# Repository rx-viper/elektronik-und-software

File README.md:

# REXUS project VIPER: Elektronik and Software

### Structure of this repository

#### *boards*
* KiCAD and mechanical files for all PCBs used in the project.

#### *software/onboard*
* Code files of microcontroller software inside the rexus module.

#### *software/groundstation*
* Code files for the groundstation software (C++/Qt).

#### *docs*
* Documentation for all above.

### HowTo do changes to this repository

* Create a new branch: `git checkout -b feature/something-i-changed`
* Do your changes.
* Tell git what files your changed and want to commit: `git add my/file.changed my/other/file.changed`
* Commit your changes: `git commit -m "Description of my changes"`
* Push your changes to Github: `git push`
* Go to Github and create a new *Pull request* from your new branch to the *master* branch.
* Wait for someone to review and merge your Pull Request.
* Then checkout the *master* brach and pull the changes from Github: `git checkout master && git pull`

Use markdown syntax for text files and `*.md` file extension.

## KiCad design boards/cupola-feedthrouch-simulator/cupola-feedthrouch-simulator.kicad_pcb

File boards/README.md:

# rexus-viper-elektronik
Rexus Viper Elektronik Projekt

## Temperature Sensor Board
* LTC2984
* <-> 6x PT-100 4-wire
* -> 5V power supply
* <- SPI data out

## Mainboard
* -> Pressure sensor (SPI/I2C)
* -> Force sensor (analog/SPI/I2C)
* -> 5x Temperature sensor SPI (Temperature Sensor Board)
* -> Heat probe voltage and current sensing
* -> DS18B20 Temperature sensors (1-wire bus)
* 3.3V regulator
* STM32F429VI microcontroller
* Data storage (flash memory chip)
* <-> RXSM communication
* <- Raspberry Pi (UART)
* -> 5V power supply
* -> Status LEDs
* <- Control panel

## Powerboard
* -> Battery
* -> RXSM power
* 3x 60W 24V step-up converter
* <- Heat probe
* <- Motor power
* -> Motor control
* <- Battery heater
* <- Mainboard power
* <- Raspbery Pi power
* <- Camera power
* <- Camera light
* -> Camera control
* -> Heat probe control
* <- Heat probe voltage and current sensing

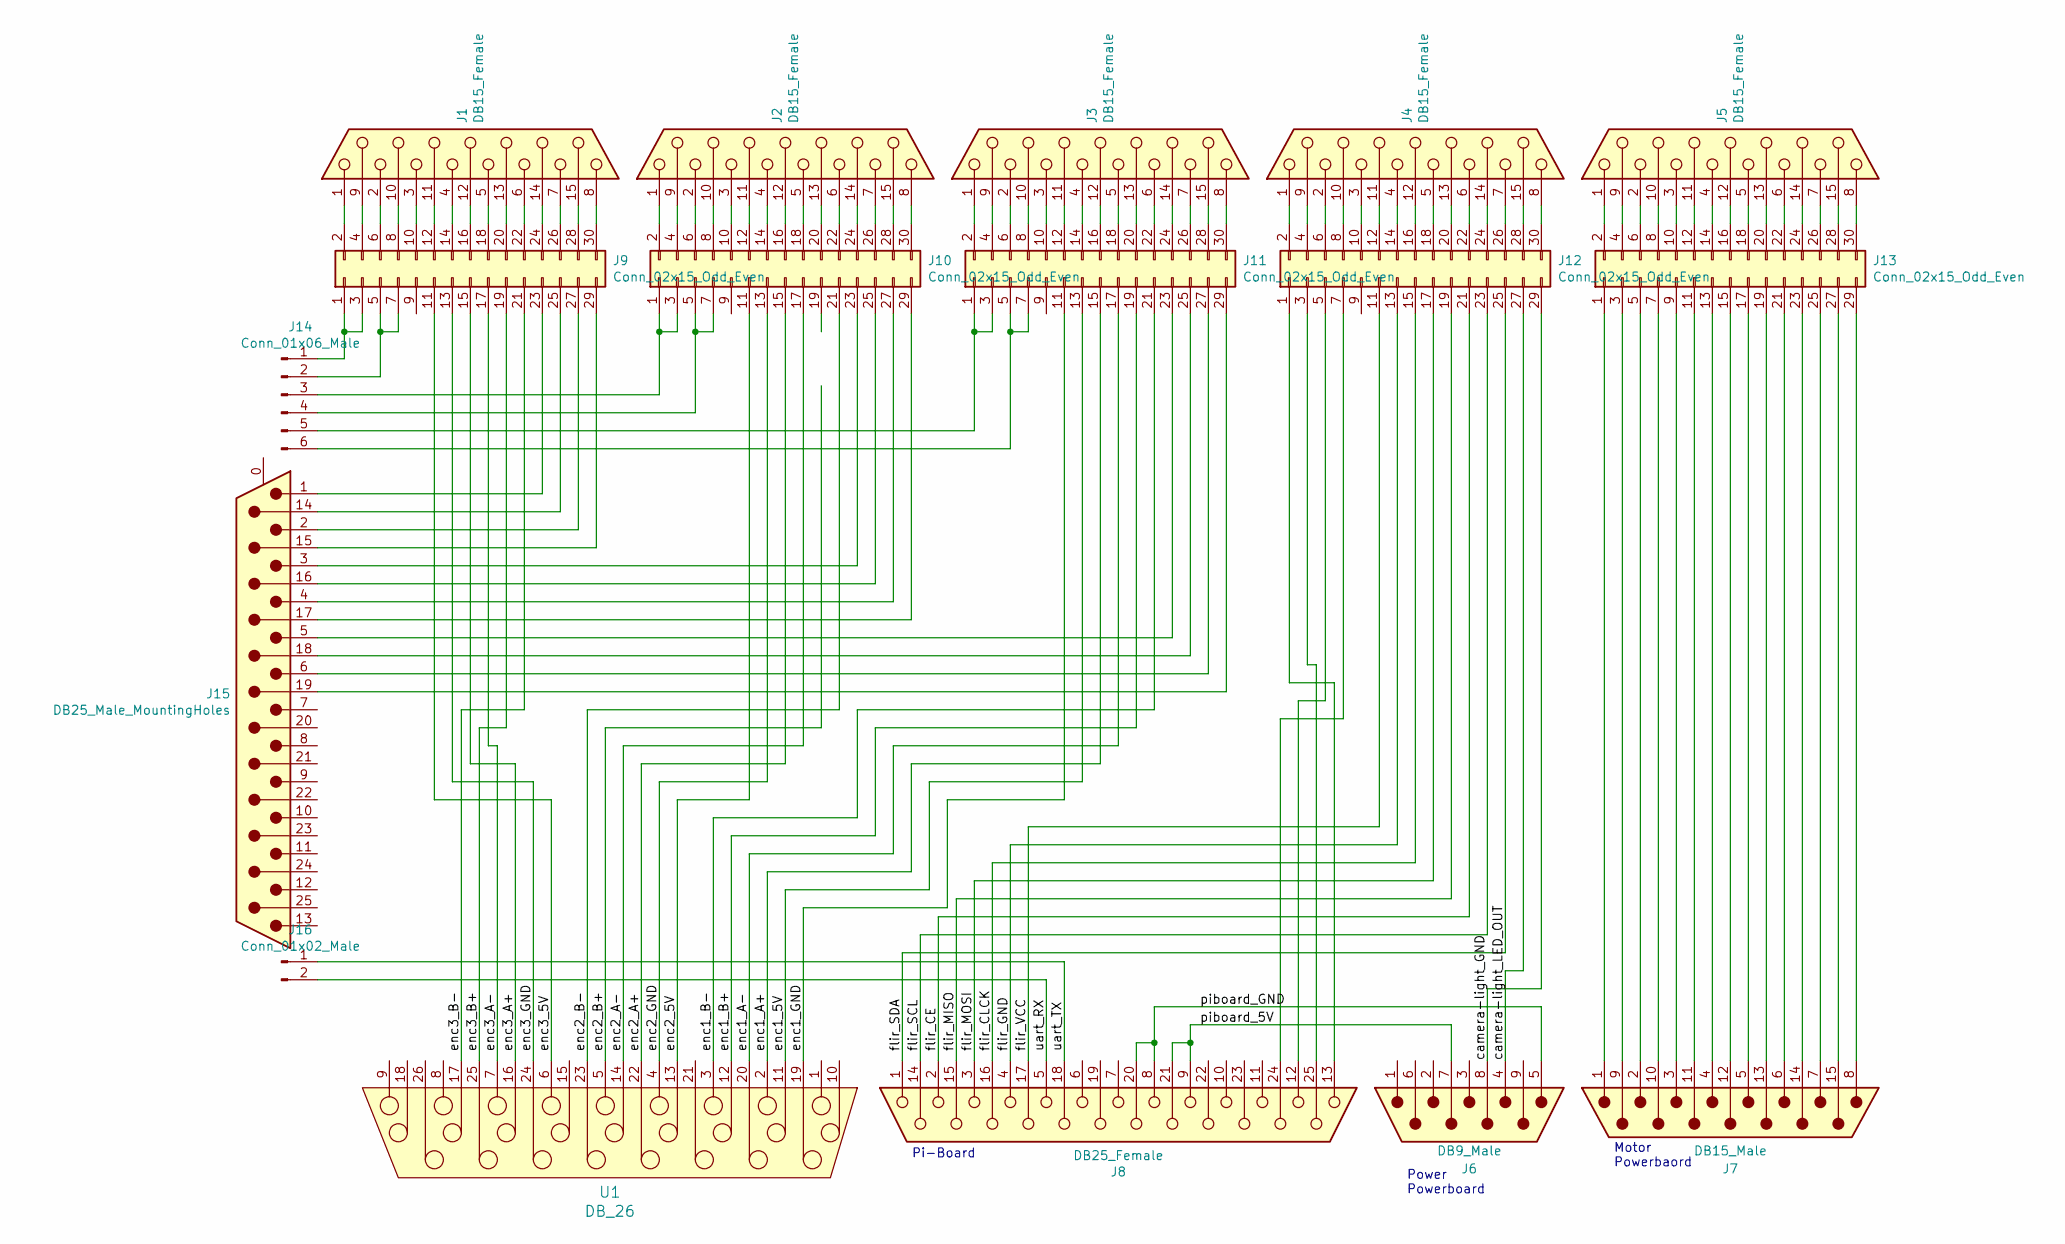
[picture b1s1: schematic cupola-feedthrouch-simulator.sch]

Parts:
J1, J2, J3, J4, J5: DB15_Female; DSUB-15_Female_Vertical_P2.77x2.84mm_MountingHoles
J6: DB9_Male; DSUB-9_Male_Vertical_P2.77x2.84mm_MountingHoles
J7: DB15_Male; DSUB-15_Male_Vertical_P2.77x2.84mm_MountingHoles
J8: DB25_Female; DSUB-25_Female_Vertical_P2.77x2.84mm_MountingHoles
J9, J10, J11, J12, J13: Conn_02x15_Odd_Even; PinHeader_2x15_P2.54mm_Vertical
J14: Conn_01x06_Male; PinHeader_1x06_P2.54mm_Vertical
J15: DB25_Male_MountingHoles; DSUB-25_Male_Vertical_P2.77x2.84mm_MountingHoles
J16: Conn_01x02_Male; PinHeader_1x02_P2.54mm_Vertical
U1: DB_26; DSUB-26-HD_Male_Vertical_P2.29x1.98mm_MountingHoles

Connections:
/camera-light_GND: J6.8, J12.29
/camera-light_LED_OUT: J6.4, J12.27
/enc1_5V: J11.13, U1.11
/enc1_A+: J11.15, U1.2
/enc1_A-: J11.17, U1.20
/enc1_B+: J11.19, U1.12
/enc1_B-: J11.21, U1.3
/enc1_GND: J11.11, U1.19
/enc2_5V: J10.11, U1.13
/enc2_A+: J10.15, U1.22
/enc2_A-: J10.17, U1.14
/enc2_B+: U1.5
/enc2_B-: J10.21, U1.23
/enc2_GND: J10.13, U1.4
/enc3_5V: J9.11, U1.6
/enc3_A+: J9.15, U1.16
/enc3_A-: J9.17, U1.7
/enc3_B+: J9.19, U1.25
/enc3_B-: J9.21, U1.17
/enc3_GND: J9.13, U1.24
/flir_CE: J8.2, J12.21
/flir_CLCK: J8.16, J12.15
/flir_GND: J8.4, J12.13
/flir_MISO: J8.15, J12.19
/flir_MOSI: J8.3, J12.17
/flir_SCL: J8.14, J12.23
/flir_SDA: J8.1, J12.25
/flir_VCC: J8.17, J12.11
/piboard_5V: J6.7, J8.9, J8.21
/piboard_GND: J6.5, J8.8, J8.20
/uart_RX: J8.5, J16.2
/uart_TX: J8.18, J16.1
unnamed: J1.1, J9.2
unnamed: J1.2, J9.6
unnamed: J1.3, J9.10
unnamed: J1.4, J9.14
unnamed: J1.5, J9.18
unnamed: J1.6, J9.22
unnamed: J1.7, J9.26
unnamed: J1.8, J9.30
unnamed: J1.9, J9.4
unnamed: J1.10, J9.8
unnamed: J1.11 (P111), J9.12
unnamed: J1.12, J9.16
unnamed: J1.13, J9.20
unnamed: J1.14, J9.24
unnamed: J1.15, J9.28
unnamed: J10.1, J10.3, J14.3
unnamed: J2.1, J10.2
unnamed: J2.9, J10.4
unnamed: J10.5, J10.7, J14.4
unnamed: J2.2, J10.6
unnamed: J2.10, J10.8
unnamed: J2.3, J10.10
unnamed: J2.11 (P111), J10.12
unnamed: J2.4, J10.14
unnamed: J2.12, J10.16
unnamed: J2.5, J10.18
unnamed: J2.13, J10.20
unnamed: J2.6, J10.22
unnamed: J10.23, J15.3
unnamed: J2.14, J10.24
unnamed: J10.25, J15.16
unnamed: J2.7, J10.26
unnamed: J10.27, J15.4
unnamed: J2.15, J10.28
unnamed: J10.29, J15.17
unnamed: J2.8, J10.30
unnamed: J11.1, J11.3, J14.5
unnamed: J3.1, J11.2
unnamed: J3.9, J11.4
unnamed: J11.5, J11.7, J14.6
unnamed: J3.2, J11.6
unnamed: J3.10, J11.8
unnamed: J3.3, J11.10
unnamed: J3.11 (P111), J11.12
unnamed: J3.4, J11.14
unnamed: J3.12, J11.16
unnamed: J3.5, J11.18
unnamed: J3.13, J11.20
unnamed: J3.6, J11.22
unnamed: J11.23, J15.5
unnamed: J3.14, J11.24
unnamed: J11.25, J15.18
unnamed: J3.7, J11.26
unnamed: J11.27, J15.6
unnamed: J3.15, J11.28
unnamed: J11.29, J15.19
unnamed: J3.8, J11.30
unnamed: J8.13, J12.1
unnamed: J4.1, J12.2
unnamed: J8.25, J12.3
unnamed: J4.9, J12.4
unnamed: J8.12, J12.5
unnamed: J4.2, J12.6
unnamed: J8.24, J12.7
unnamed: J4.10, J12.8
unnamed: J4.3, J12.10
unnamed: J4.11 (P111), J12.12
unnamed: J4.4, J12.14
unnamed: J4.12, J12.16
unnamed: J4.5, J12.18
unnamed: J4.13, J12.20
unnamed: J4.6, J12.22
unnamed: J4.14, J12.24
unnamed: J4.7, J12.26
unnamed: J4.15, J12.28
unnamed: J4.8, J12.30
unnamed: J7.1, J13.1
unnamed: J5.1, J13.2
unnamed: J7.9, J13.3
unnamed: J5.9, J13.4
unnamed: J7.2, J13.5
unnamed: J5.2, J13.6
unnamed: J7.10, J13.7
unnamed: J5.10, J13.8
unnamed: J7.3, J13.9
unnamed: J5.3, J13.10
unnamed: J7.11 (P111), J13.11
unnamed: J5.11 (P111), J13.12
unnamed: J7.4, J13.13
unnamed: J5.4, J13.14
unnamed: J7.12, J13.15
unnamed: J5.12, J13.16
unnamed: J7.5, J13.17
unnamed: J5.5, J13.18
unnamed: J7.13, J13.19
unnamed: J5.13, J13.20
unnamed: J7.6, J13.21
unnamed: J5.6, J13.22
unnamed: J7.14, J13.23
unnamed: J5.14, J13.24
unnamed: J7.7, J13.25
unnamed: J5.7, J13.26
unnamed: J7.15, J13.27
unnamed: J5.15, J13.28
unnamed: J7.8, J13.29
unnamed: J5.8, J13.30
unnamed: J9.1, J9.3, J14.1
unnamed: J9.5, J9.7, J14.2
unnamed: J9.23, J15.1
unnamed: J9.27, J15.2
unnamed: J9.25, J15.14
unnamed: J9.29, J15.15

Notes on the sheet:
Motor Powerbaord
Power Powerboard
Pi-Board

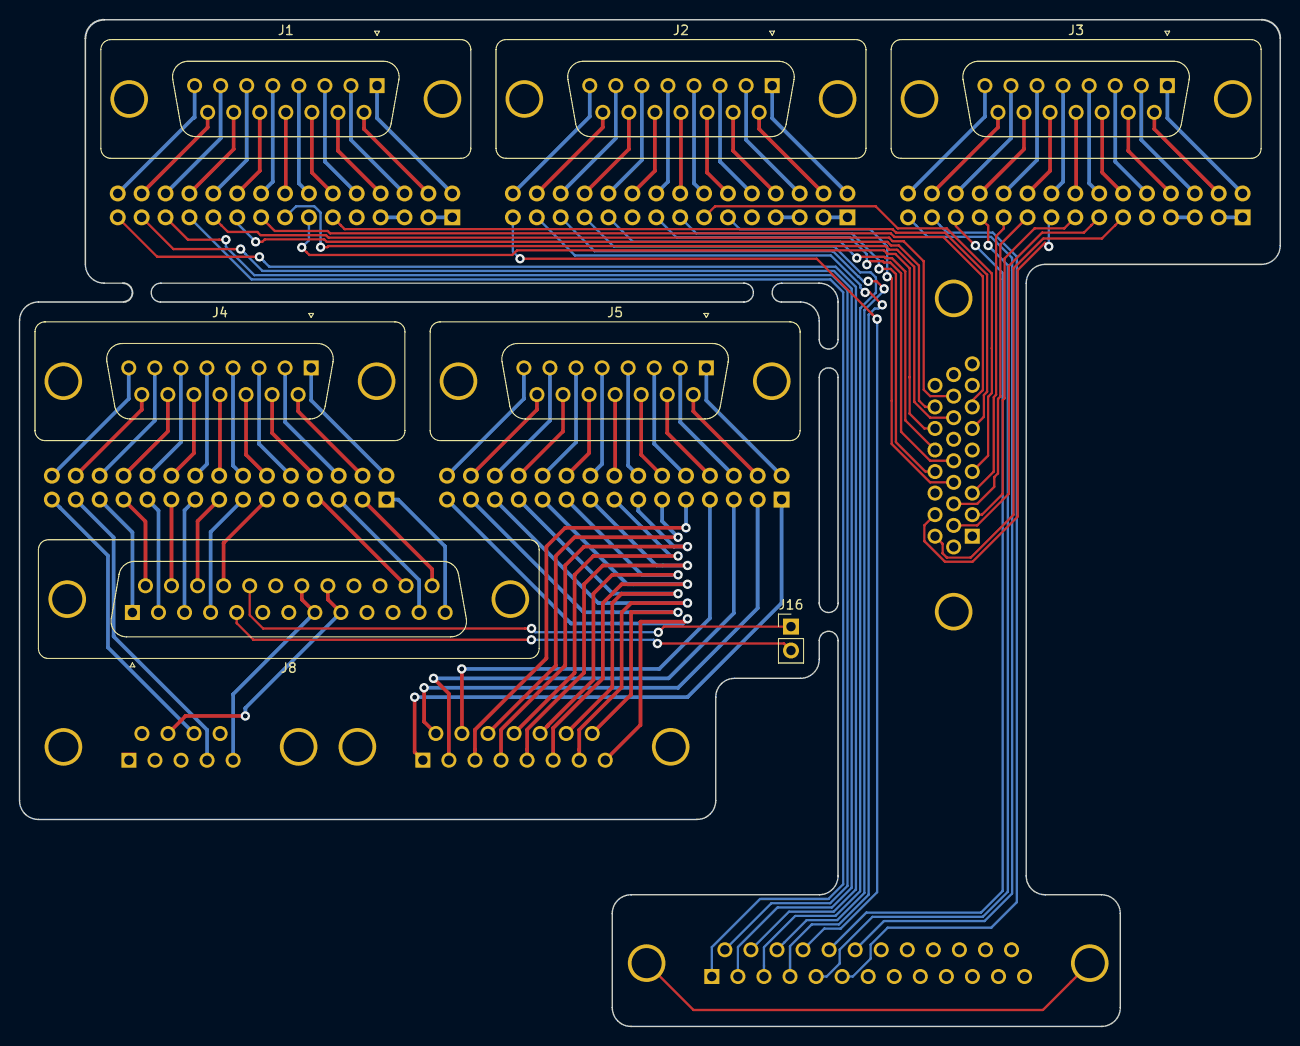
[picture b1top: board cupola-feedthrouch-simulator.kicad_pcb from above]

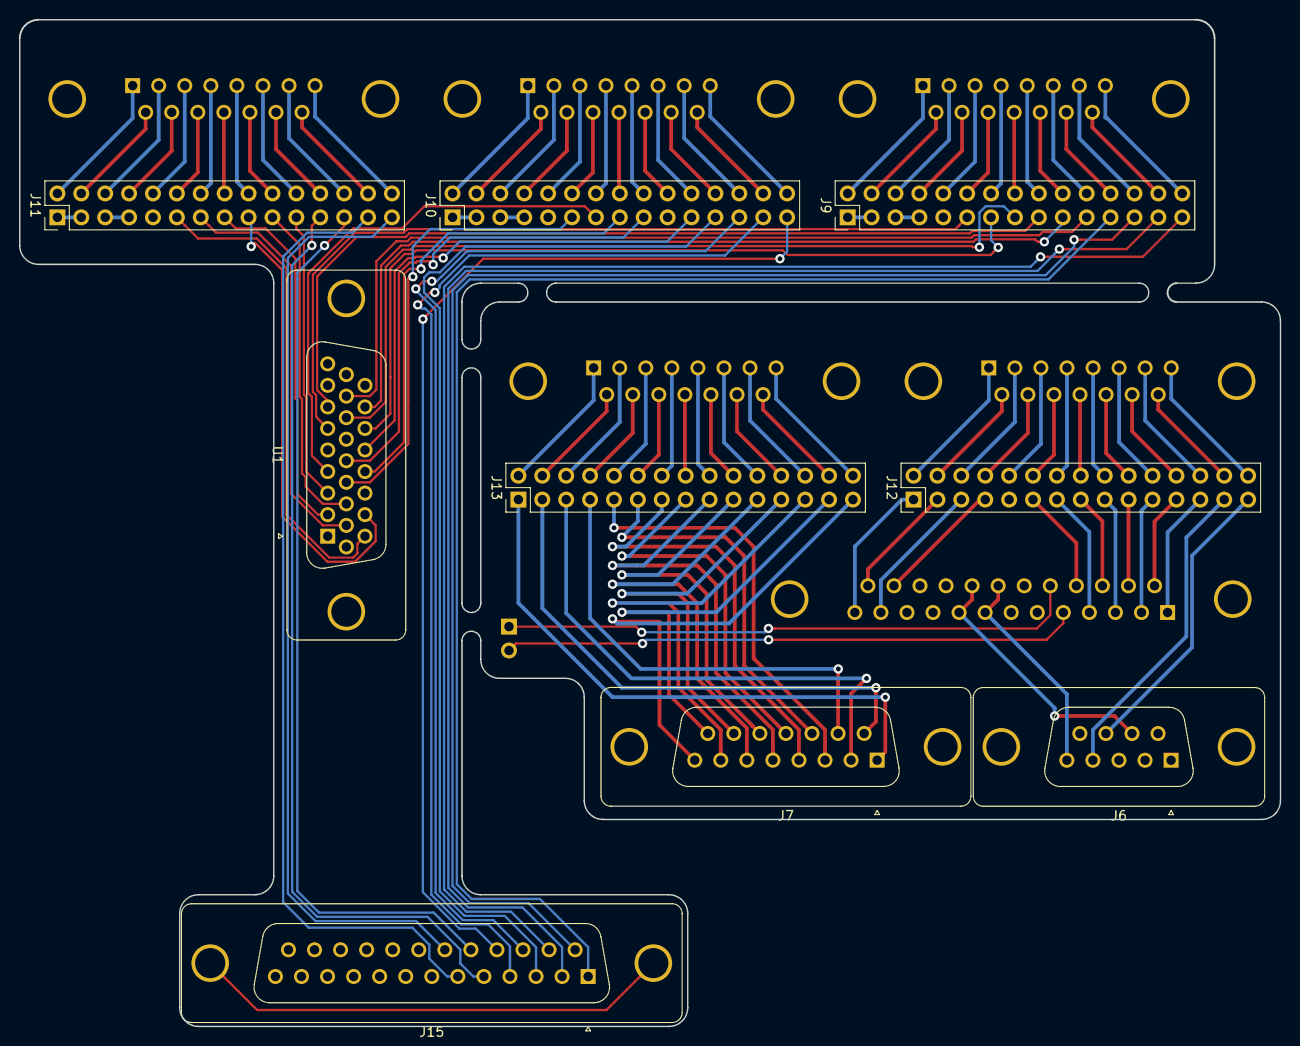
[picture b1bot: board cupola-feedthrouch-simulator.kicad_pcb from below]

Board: 2 copper layers, 134.0 x 107.0 mm, 16 parts (9 on the bottom side), 143 nets.

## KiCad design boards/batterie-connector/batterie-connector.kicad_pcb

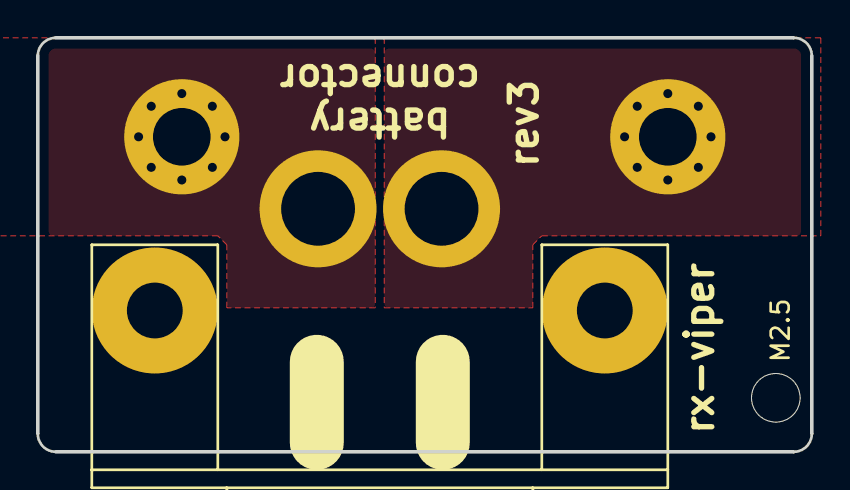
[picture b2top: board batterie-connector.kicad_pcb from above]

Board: 2 copper layers, 43.0 x 23.0 mm, 4 parts (0 on the bottom side), 2 nets, no tracks yet.

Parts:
H101: M2.5; MountingHole_2.7mm_M2.5_DIN965
J101: 2W2C; D-Sub-Combo_2W2C
J102: +; MountingHole_3.2mm_M3_Pad_Via
J103: -; MountingHole_3.2mm_M3_Pad_Via

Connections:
/MINUS: J101.2, J103.1
/PLUS: J101.1, J102.1

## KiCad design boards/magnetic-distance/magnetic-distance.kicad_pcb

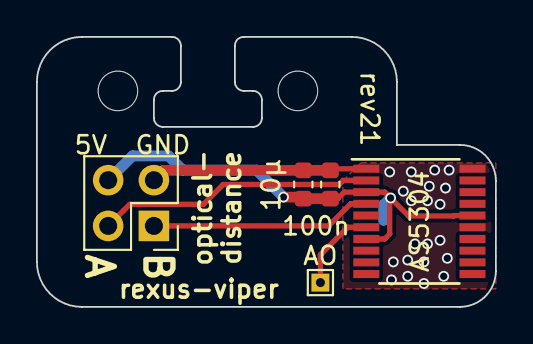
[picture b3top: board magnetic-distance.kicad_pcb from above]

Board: 2 copper layers, 25.5 x 15.0 mm, 8 parts (1 on the bottom side), 5 nets.

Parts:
C101: 100n; C_0603_1608Metric
C102: 10µ; C_0603_1608Metric
H101, H102: M2; MountingHole_2.2mm_M2
J101: Cable; PinHeader_2x02_P2.54mm_Vertical
R_HEAT101: 100; R_0805_2012Metric
TP101: AO; TestPoint_THTPad_1.0x1.0mm_Drill0.5mm
U101: AS5304; TSSOP-20_4.4x6.5mm_P0.65mm

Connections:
+5V: C101.1, C102.1, J101.4, R_HEAT101.1, U101.3, U101.7, U101.16
/A: J101.2, U101.2
/AO: TP101.1, U101.6
/B: J101.1, U101.4
GND: C101.2, C102.2, J101.3, R_HEAT101.2, U101.1, U101.15, U101.20

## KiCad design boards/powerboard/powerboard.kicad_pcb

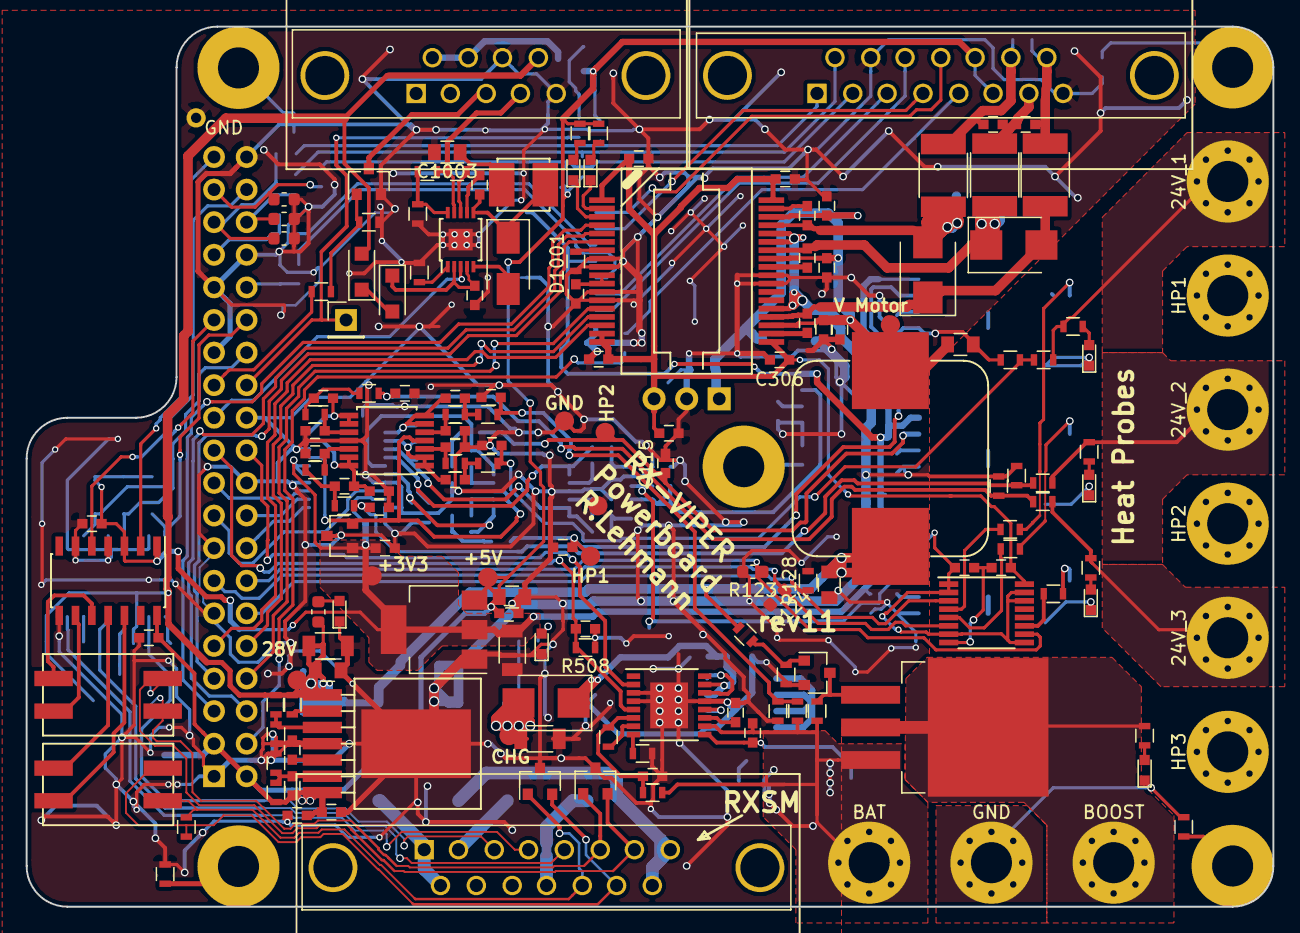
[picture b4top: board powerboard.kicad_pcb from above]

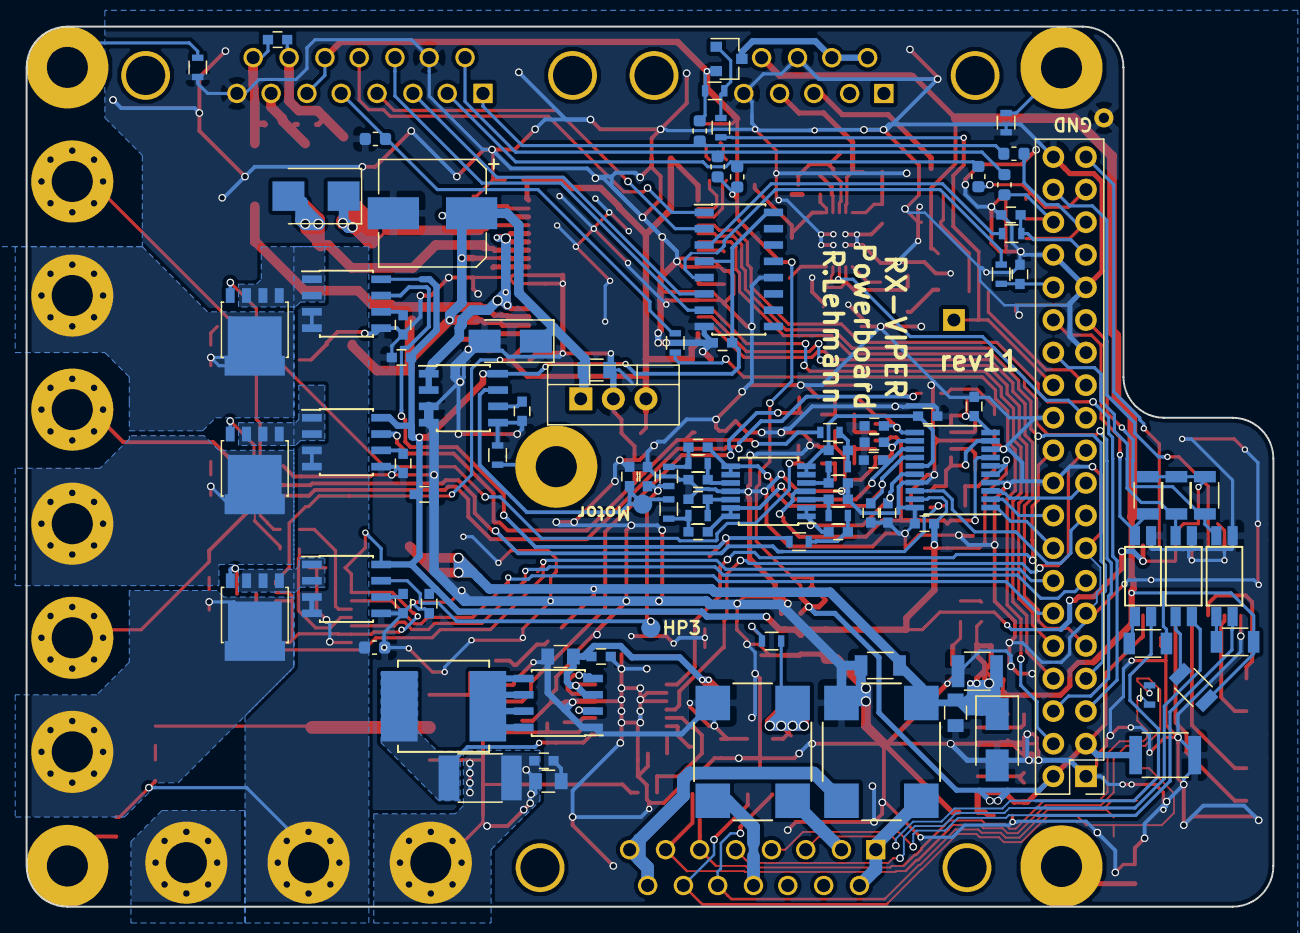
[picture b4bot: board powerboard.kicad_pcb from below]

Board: 2 copper layers, 97.2 x 68.6 mm, 268 parts (97 on the bottom side), 174 nets.

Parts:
C101: 10µ; C_1206
C102: 4µ7 1206 50V; C_1206
C103: 1µ; C_0805
C104: 10µ oder 4µ7 Tantal; C_0805
C105, C109, C302, C304, C305, C306, C308, C309, C310, C312, C315, C504, C506, C701, C801, C802, C803, C901, C902, C1002, C1201, C1202: 100n; C_0603
C106: 470n; C_0805
C107, C121: 2n7; C_0603
C108: 22µ Tantal; C_1206
C110, C111, C112, C113, C114, C115, C116, C117, C205, C910, C911, C912, C913, C914, C915, C916, C917: 10n; C_0603
C118: 10µ 1210; C_1210
C119: 1µ 0805 50V; C_0805
C120: 50SVPK68M; CP_Elec_8x10.5
C122, C123, C124: 22n; C_0603_1608Metric
C201: 10µ/40V; C_1206
C202: 1µ/40V; C_0805
C203, C204: 22n; C_0603
C206: 100µ/10V; C_1812
C207, C307, C314, C702, C1001: 1µ; C_0603
C301: 4µ7 0805; C_0805
C303: 10µ; C_0603
C313: 4µ7 0805; C_0603
C316, C317, C318: 100p; C_0603
C319, C804, C805, C806: 1n; C_0603
C501: 68n; C_0603
C502: 47n; C_0603
C503: 10µ 0805 35V; C_0805
C505: 10µ; C_0805
C507: 470n; C_0603
C508, C1101, C1102, C1103, C1104, C1105, C1106, C1107, C1108, C1109, C1110, C1111, C1112, C1113, C1114, C1115, C1116: 220n; C_0603
C1003: 4µ7 0805 50V; C_0805
D101: RX-PW; LED_0603
D102: RX-CHG; LED_0603
D103: BAT; LED_0603
D104, D105: SMAJ36A; D_SMA
D301, D302: LED; LED_0603
D304, D305, D306: SMBJ40CA; D_SMB_Standard
D501: MBRS360BT3G; D_SMB_Standard
D701, D702: ESD; SOT-23
D801: HP1; LED_0603
D802: HP2; LED_0603
D803: HP3; LED_0603
D1001: MBRA140T3; D_SMA_Standard
D1002, D1003: US1NWF; D_SOD-123F
FL101, FL102: 744272471; WE-SL5
FL701, FL702: 744228; WE-SL2
J101: RXSM experiment connector; DB15MD
J102: Powerboard <-> Mainboard; Pin_Header_Straight_2x20_Pitch2.54mm
J103: Cameraboard; DB9FD
J104: BLDC Motor; DB15FD
J105: BOOST; MountingHole_3.2mm_M3_Pad_Via
J106: Boost24V_EN; Pin_Header_Straight_1x01_Pitch2.54mm
J107: 24V_1; MountingHole_3.2mm_M3_Pad_Via
J108: 24V_2; MountingHole_3.2mm_M3_Pad_Via
J109: 24V_3; MountingHole_3.2mm_M3_Pad_Via
J110: BAT; MountingHole_3.2mm_M3_Pad_Via
J111: GND; MountingHole_3.2mm_M3_Pad_Via
J112, J113, J114, J115, J117: M3; MountingHole_3.2mm_M3_Pad
J810: HP1; MountingHole_3.2mm_M3_Pad_Via
J811: HP2; MountingHole_3.2mm_M3_Pad_Via
J812: HP3; MountingHole_3.2mm_M3_Pad_Via
L101: Coilcraft MSS1583-474; L_Coilcraft_1583_Handsoldering
L301, L302, L303: 742792515; L_1812
L501: Coilcraft XAL6060-223; L_Coilcraft_XAL60xx_Handsoldering
L1001: Coilcraft XAL4040-103; L_Coilcraft_XAL40xx_Handsoldering
Q101: SQM40031EL; TO-263-3Lead
Q102: DMN6140L; SOT-23
Q103: PMV27UPE; SOT-23
Q104: PMV55ENEA; SOT-23
Q503: IRF7343PBF; SOIC-8_3.9x4.9mm_Pitch1.27mm
Q801, Q802, Q803: BUK7Y4R8-60E; SOT-669_LFPAK
R101, R103, R126, R128, R508, R801, R802, R803, R807, R808, R809: 10k; R_0603
R102: 20k; R_0603
R104: 91k; R_0603
R105: 13k; R_0603
R106, R108, R113: 15k; R_0603
R107, R109, R110, R114, R130, R607, R608: 1k; R_0603
R111: 0; R_0603
R112, R129, R1002: 100k; R_0603
R115, R116, R117, R118, R120: NC; R_0603
R119, R121: 100; R_0603
R122: 0; R_0603_1608Metric
R123, R124, R125: 10k; R_0603_1608Metric
R127: 4k; R_0603
R131, R132, R133, R137: 4k7; R_0603_1608Metric
R134, R135, R136: 470; R_0603_1608Metric
R201: 68k1; R_0603
R202: 11k8; R_0603
R203: 43k2; R_0603
R204: 5k62; R_0603
R205: 1k07; R_0603
R301, R302: 470; R_0603
R303: 200k; R_0603
R504: 65k7; R_0603
R505: 8k2; R_0603
R506: 50k; R_0603
R507: 100m; R_1812
R601, R602, R603, R604, R605, R606: 10k 1206; R_1206
R1001: 140k; R_0603
R1003: 4k7; R_0603
R1004: 2R; R_0603
R1101, R1102, R1103, R1104, R1105, R1106, R1107, R1108, R1109, R1110, R1111, R1112, R1113, R1114, R1115, R1116: 47k; R_0603
TP101: 28V; Measurement_Point_Round-SMD-Pad_Small
TP102: CHG; Measurement_Point_Round-SMD-Pad_Small
TP103: +5V; Measurement_Point_Round-SMD-Pad_Small
TP104: +3V3; Measurement_Point_Round-SMD-Pad_Small
TP105, TP106: GND; Measurement_Point_Round-SMD-Pad_Small
TP107: HP3C; Measurement_Point_Round-SMD-Pad_Small
TP108: GND; Measurement_Point_Round-TH_Small
TP109: HP2C; Measurement_Point_Round-SMD-Pad_Small
TP110: HP1C; Measurement_Point_Round-SMD-Pad_Small
TP111: V_MOTOR; Measurement_Point_Round-SMD-Pad_Small
TP112: MOTORC; Measurement_Point_Round-SMD-Pad_Small
U101: LM1117-3.3; SOT-223
U102: DS26LV32AT; SOIC-16_3.9x9.9mm_Pitch1.27mm
U201: LMZ14203; 7TO-PMOD
U301: 7812SR-C; TO-220_Vertical
U302: DRV8332; HSSOP-36
U303, U801, U802, U803: ACS711; SOIC-8_3.9x4.9mm_Pitch1.27mm
U501: LTC4010; TSSOP-16-1EP_4.4x5mm_Pitch0.65mm
U601, U602, U603: PC3H7; SOP-4
U701: MAX13432EESD; SOIC-14_3.9x8.7mm_Pitch1.27mm
U901: AD7928; TSSOP-20_4.4x6.5mm_Pitch0.65mm
U902: REF3025; SOT-23
U1001: LT3592; MSOP-10-1EP_3x3mm_Pitch0.5mm
U1101, U1102: LMV324; TSSOP-14_4.4x5mm_Pitch0.65mm
U1201: CD40109B; TSSOP-16_4.4x5mm_Pitch0.65mm

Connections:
+2V5: U901.7, U902.2, U1101.4, U1102.4
+3V3: C108.1, C109.1, C701.1, C801.1, C802.1, C803.1, C901.1, C902.1, C1201.1, R601.2, R602.2, R603.2, TP104.1, U101.2, U101.4, U102.4, U102.16, U303.8, U701.1, U701.3, U801.8, U802.8, U803.8, U901.5, U901.6, U901.19, U902.1, U1201.1, U1201.2, U1201.7, U1201.9, U1201.14, U1201.15
+5V: C104.1, C105.1, C204.1, C205.1, C206.1, C207.1, C702.1, J102.2, J102.3, J104.6, J104.13, Q103.2, R129.2, R131.1, R132.1, R133.1, R204.1, R301.2, R302.2, TP103.1, U101.3, U201.7, U701.14
+12V: C302.1, C303.1, C304.1, C306.1, C312.1, C1202.1, U301.3, U302.1, U302.17, U302.18, U302.19, U302.36, U1201.16
/24V_BAT_1: J107.1, R113.1, R807.2
/24V_BAT_2: J108.1, R108.1, R808.2
/24V_BAT_3: J109.1, R106.1, R809.2
/BAT_10V: J105.1, Q101.2, R127.2
/BAT_raw: C505.1, C506.1, C507.1, J110.1, Q101.3, R101.1, R104.1, R504.1, R507.2, U501.10
/Boost24V_EN: J102.26, J106.1, R130.2
/Cam_Light_EN: J102.23, U1001.3
/Charge_EN: C501.1, J102.21, R508.2, U501.5
/Charge_status: J102.22, U501.2
/Encoder_A: C107.1, J102.32, R119.1
/Encoder_A+: J104.3, U102.6
/Encoder_A-: J104.11, U102.7
/Encoder_A_filter: R119.2, U102.5
/Encoder_B: C121.1, J102.33, R121.1
/Encoder_B+: J104.4, U102.2
/Encoder_B-: J104.12, U102.1
/Encoder_B_filter: R121.2, U102.3
/EndSwitch: J102.4, R111.1
/Hall_U: J104.1, R133.2, R134.1
/Hall_U_filter: C122.1, J102.35, R134.2
/Hall_V: J104.9, R132.2, R135.1
/Hall_V_filter: C123.1, J102.36, R135.2
/Hall_W: J104.2, R131.2, R136.1
/Hall_W_filter: C124.1, J102.37, R136.2
/LO: J102.28, R601.1, U601.4
/Lens_Heat_EN: J102.25, R110.2
/Motor1_Current: C117.1, R1104.2, TP112.1, U303.7
/Motor_U_N: J102.6, U302.5
/Motor_U_P: J102.5, U302.4
/Motor_V_N: J102.8, U302.14
/Motor_V_P: J102.7, U302.6
/Motor_W_N: J102.10, U302.15
/Motor_W_P: J102.9, U302.16
/Phase_U: C317.1, C318.2, J104.14, L301.2
/Phase_V: C316.1, C317.2, J104.7, L302.2
/Phase_W: C316.2, C318.1, J104.15, L303.2
/Powerboard Battery Charging/bat_bgate: Q503.2, U501.12
/Powerboard Battery Charging/bat_inductor: L501.1, Q503.5, Q503.6, Q503.7, Q503.8
/Powerboard Battery Charging/bat_sense: C507.2, L501.2, R507.1, U501.9
/Powerboard Battery Charging/bat_tgate: Q503.4, U501.14
/Powerboard Battery Charging/charge_power: C101.1, D501.2, FL102.2, R126.2, TP102.1
/Powerboard Motor Controller/VREG: C305.1, U302.10, U302.11
/Powerboard Motor Controller/V_IN: C106.1, C120.1, C301.1, C307.1, C313.1, C314.1, C315.1, D105.1, L101.2, TP111.1, U301.1, U302.21, U302.29, U302.34
/Powerboard_ADC/IN0: C910.1, C1105.1, U901.16, U1101.1, U1101.2
/Powerboard_ADC/IN1: C911.1, C1106.1, U901.15, U1101.6, U1101.7
/Powerboard_ADC/IN2: C912.1, C1107.1, U901.14, U1101.8, U1101.9
/Powerboard_ADC/IN3: C913.1, C1108.1, U901.13, U1101.13, U1101.14
/Powerboard_ADC/IN4: C914.1, C1113.1, U901.12, U1102.1, U1102.2
/Powerboard_ADC/IN5: C915.1, C1114.1, U901.11, U1102.6, U1102.7
/Powerboard_ADC/IN6: C916.1, C1115.1, U901.10, U1102.8, U1102.9
/Powerboard_ADC/IN7: C917.1, C1116.1, U901.9, U1102.13, U1102.14
/Powerboard_ADC_Filter/IN4: C113.1, R113.2, R114.1, R1109.2
/Powerboard_ADC_Filter/IN5: C110.1, R104.2, R105.1, R1110.2
/Powerboard_ADC_Filter/IN6: C111.1, R106.2, R107.1, R1111.2
/Powerboard_ADC_Filter/IN7: C112.1, R108.2, R109.1, R1112.2
/Powerboard_Heat_Probes/Probe1: D801.1, J810.1, Q801.5
/Powerboard_Heat_Probes/Probe1_sense: Q801.1, Q801.2, Q801.3, U801.1, U801.2
/Powerboard_Heat_Probes/Probe2: D802.1, J811.1, Q802.5
/Powerboard_Heat_Probes/Probe2_sense: Q802.1, Q802.2, Q802.3, U802.1, U802.2
/Powerboard_Heat_Probes/Probe3: D803.1, J812.1, Q803.5
/Powerboard_Heat_Probes/Probe3_sense: Q803.1, Q803.2, Q803.3, U803.1, U803.2
/Powerboard_LED_driver/LED_OUT: J103.4, R1002.2, R1004.2, U1001.9
/Powerboard_MOSFET_Driver/OUT_A: R801.2, U1201.4
/Powerboard_MOSFET_Driver/OUT_B: R802.2, U1201.5
/Powerboard_MOSFET_Driver/OUT_C: R803.2, U1201.11
/Probe1_Current: C116.1, R1101.2, TP110.1, U801.7
/Probe1_EN: J102.12, R128.1, U1201.3
/Probe2_Current: C115.1, R1102.2, TP109.1, U802.7
/Probe2_EN: J102.13, R124.1, U1201.6
/Probe3_Current: C114.1, R1103.2, TP107.1, U803.7
/Probe3_EN: J102.14, R123.1, U1201.10
/RX: J102.39, U701.2
/RXSM_28V: C102.1, C103.1, C118.1, C119.1, C201.1, C202.1, D104.1, D1002.2, FL101.2, J103.9, L101.1, R102.2, R125.2, R201.1, R203.2, R604.1, R605.1, R606.1, TP101.1, U201.1
/RXSM_Ground: FL101.4, J101.8, J101.15
/RXSM_LO: J101.5, U601.2
/RXSM_RX_A: D702.1, FL701.2, J101.13, R608.1
/RXSM_RX_Y: D701.1, FL702.2, J101.6, R607.1
/RXSM_RX_~B: D702.2, FL701.3, J101.14, R608.2
/RXSM_RX_~Z: D701.2, FL702.3, J101.7, R607.2
/RXSM_SODS: J101.3, U603.2
/RXSM_SOE: J101.4, U602.2
/RXSM_charge+: FL102.1, J101.2
/RXSM_charge-: FL102.4, J101.12
/RXSM_power: FL101.1, J101.1, J101.9
/SODS: J102.30, R603.1, U603.4
/SOE: J102.29, R602.1, U602.4
/TX: J102.38, U701.5
/extADC_SPI_CS1: J102.19, U901.3
/extADC_SPI_MISO: J102.17, U901.18
/extADC_SPI_MOSI: J102.18, U901.2
/extADC_SPI_SCK: J102.16, U901.1
GND: C101.2, C102.2, C103.2, C104.2, C105.2, C106.2, C107.2, C108.2, C109.2, C110.2, C111.2, C112.2, C113.2, C114.2, C115.2, C116.2, C117.2, C118.2, C119.2, C120.2, C121.2, C122.2, C123.2, C124.2, C201.2, C202.2, C203.2, C205.2, C206.2, C207.2, C301.2, C302.2, C303.2, C304.2, C305.2, C306.2, C307.2, C312.2, C313.2, C314.2, C315.2, C319.2, C501.2, C502.2, C503.2, C504.2, C505.2, C506.2, C508.2, C701.2, C702.2, C801.2, C802.2, C803.2, C804.2, C805.2, C806.2, C901.2, C902.2, C910.2, C911.2, C912.2, C913.2, C914.2, C915.2, C916.2, C917.2, C1001.1, C1003.2, C1101.2, C1102.2, C1103.2, C1104.2, C1109.2, C1110.2, C1111.2, C1112.2, D101.1, D102.1, D104.2, D105.2, D701.3, D702.3, FL101.3, FL102.3, J102.1, J102.11, J102.15, J102.20, J102.24, J102.27, J102.31, J102.34, J102.40, J103.5, J103.8, J104.8, J104.10, Q102.2, Q104.2, Q503.1, R103.2, R105.2, R107.2, R109.2, R112.1, R114.2, R115.2, R116.2, R118.2, R120.2, R122.1, R123.2, R124.2, R128.2, R137.2, R202.2, R205.2, R303.2, R506.2, R508.1, R1001.2, R1003.2, TP105.1, TP106.1, TP108.1, U101.1, U102.8, U102.12, U201.4, U201.8, U301.2, U302.8, U302.9, U302.12, U302.13, U302.26, U302.27, U303.3, U303.4, U303.5, U501.3, U501.4, U501.13, U501.17, U601.3, U602.3, U603.3, U701.4, U701.6, U701.8, U801.5, U802.5, U803.5, U901.4, U901.8, U901.17, U901.20, U902.3, U1001.11, U1101.11, U1102.11
GNDPWR: C1201.2, C1202.2, D103.1, J111.1, R117.2, R122.2, U801.3, U801.4, U802.3, U802.4, U803.3, U803.4, U1201.8
unnamed: C203.1, U201.5
unnamed: C204.2, R204.2, R205.1, U201.6
unnamed: C308.1, D305.1, D306.2, L301.1, U302.33
unnamed: C308.2, U302.35
unnamed: C309.1, D304.1, D305.2, L302.1, U302.30
unnamed: C309.2, U302.28
unnamed: C310.1, D304.2, D306.1, L303.1, U302.22
unnamed: C310.2, U302.20
unnamed: C319.1, U303.6
unnamed: C502.1, R504.2, R505.2, U501.6
unnamed: C503.1, C508.1, D501.1, Q503.3, U501.15
unnamed: C504.1, U501.11
unnamed: C804.1, U801.6
unnamed: C805.1, U802.6
unnamed: C806.1, U803.6
unnamed: C1001.2, D1003.1, U1001.2, U1001.4
unnamed: C1002.1, D1001.1, L1001.1, U1001.6
unnamed: C1002.2, U1001.7
unnamed: C1003.1, L1001.2, R1004.1, U1001.8
unnamed: C1101.1, R1105.1, U1101.3
unnamed: C1102.1, R1106.1, U1101.5
unnamed: C1103.1, R1107.1, U1101.10
unnamed: C1104.1, R1108.1, U1101.12
unnamed: C1105.2, R1101.1, R1105.2
unnamed: C1106.2, R1102.1, R1106.2
unnamed: C1107.2, R1103.1, R1107.2
unnamed: C1108.2, R1104.1, R1108.2
unnamed: C1109.1, R1113.1, U1102.3
unnamed: C1110.1, R1114.1, U1102.5
unnamed: C1111.1, R1115.1, U1102.10
unnamed: C1112.1, R1116.1, U1102.12
unnamed: C1113.2, R1109.1, R1113.2
unnamed: C1114.2, R1110.1, R1114.2
unnamed: C1115.2, R1111.1, R1115.2
unnamed: C1116.2, R1112.1, R1116.2
unnamed: D101.2, R125.1
unnamed: D102.2, R126.1
unnamed: D103.2, R127.1
unnamed: D301.1, U302.2
unnamed: D301.2, R301.1
unnamed: D302.1, U302.3
unnamed: D302.2, R302.1
unnamed: D801.2, R807.1
unnamed: D802.2, R808.1
unnamed: D803.2, R809.1
unnamed: D1001.2, U1001.5
unnamed: D1002.1, D1003.2
unnamed: FL701.1, U701.12
unnamed: FL701.4, U701.11
unnamed: FL702.1, U701.9
unnamed: FL702.4, U701.10
unnamed: J103.3, Q104.3
unnamed: J103.6, J103.7, Q103.3
unnamed: J104.5, R111.2, R137.1
unnamed: J112.1, R115.1
unnamed: J113.1, R116.1
unnamed: J114.1, R117.1
unnamed: J115.1, R118.1
unnamed: J117.1, R120.1
unnamed: Q101.1, Q102.3, R101.2
unnamed: Q102.1, R102.1, R103.1
unnamed: Q103.1, R129.1, R130.1
unnamed: Q104.1, R110.1, R112.2
unnamed: Q801.4, R801.1
unnamed: Q802.4, R802.1
unnamed: Q803.4, R803.1
unnamed: R201.2, R202.1, U201.3
unnamed: R203.1, U201.2
unnamed: R303.1, U302.7
unnamed: R505.1, U501.7
unnamed: R506.1, U501.8
unnamed: R604.2, U603.1
unnamed: R605.2, U602.1
unnamed: R606.2, U601.1
unnamed: R1001.1, U1001.1
unnamed: R1002.1, R1003.1, U1001.10
unnamed: U302.23, U302.31, U302.32, U303.1, U303.2

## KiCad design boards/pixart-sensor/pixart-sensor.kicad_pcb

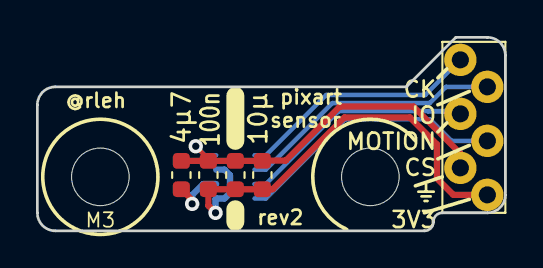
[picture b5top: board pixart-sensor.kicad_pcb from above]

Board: 2 copper layers, 26.0 x 10.8 mm, 8 parts (1 on the bottom side), 7 nets.

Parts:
C101: 10µ; C_0603_1608Metric
C102: 100n; C_0603_1608Metric
C103: 4µ7; C_0603_1608Metric
H101, H102: M3; MountingHole_3.2mm_M3
J101: Adapter; PinHeader_Custom_2x03_Versetzt
R101: HEAT; R_0603_1608Metric
U101: PAT9125EL

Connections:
+3V3: C101.1, C102.1, J101.1, R101.1, U101.1, U101.3
/ID,~CS: J101.3, U101.8
/MOTION: J101.4, U101.7
/SCA,SDIO: J101.5, U101.6
/SCL,SCLK: J101.6, U101.5
GND: C101.2, C102.2, C103.2, J101.2, R101.2, U101.4
unnamed: C103.1, U101.2

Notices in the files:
boards/lt3757-boost-converter/lt3757-boost-converter.kicad_pcb:
© Raphael
